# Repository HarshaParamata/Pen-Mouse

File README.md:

#  Pen Mouse – A Wireless Pen-Style Mouse using ATmega328P

The **Pen Mouse** is a compact, pen-like input device that functions similarly to a traditional mouse. It uses an optical sensor to detect movement and buttons for left/right click functionality. Built using affordable and widely available components, this device is ideal for students, designers, and users with limited desk space—particularly during presentations or graphic design work.

---

##  Features

- Move the cursor and perform clicks
- Pen-like ergonomic design for precise control
- Communicates wirelessly via Bluetooth
- Rechargeable and portable

---

##  Components Selection

- **ATmega328P-PU Microcontroller**  
  8-bit AVR RISC-based MCU with DIP-28 package for easy prototyping. Offers sufficient I/O, memory, and Arduino compatibility.

- **HC-06 Bluetooth Module (4-pin)**  
  Provides wireless connectivity. Simple UART interface, works with 3.3V or 5V logic.

- **TPS61023DRLT Switching Regulator**  
  Ensures stable 5V output from a Li-ion battery input, essential for reliable operation.
- **MX8733 Optical Sensor**
   it will track the movement of mouse send to microcontroller.
- **Li-ion Battery**  
  Rechargeable power source for portable use.

- **Arduino Uno**  
  Used for uploading firmware to the ATmega328P.

- **Passive Components (Resistors, Capacitors)**  
  For pull-ups, filtering, and power stabilization.

---
##  Getting Started

###  PCB Design

- The ATmega328P is placed centrally with decoupling capacitors near its power pins.
- SPI lines (MOSI, MISO, SCK, SS) are routed to the HC-06 Bluetooth module via pins 10–13 on the ATmega.
- A voltage regulation circuit using TPS61023DRLT generates a stable 5V from the Li-ion battery.

###  Uploading Code to ATmega328P

1. Use an **Arduino Uno as ISP** to program the ATmega328P.
2. Follow this official Arduino tutorial for setup and connections:  
    [How to program ATmega328P using Arduino Uno – Arduino to Breadboard](https://docs.arduino.cc/built-in-examples/arduino-isp/ArduinoToBreadboard/)
3. Or follow the  [youtude tutorials](https://youtube.com/playlist?list=PLtuqBdbsL-DvbB6QAGgoGBAEsGuXfGFoF&feature=shared).
4. Flash the Pen Mouse firmware (provided in the `codes/` folder).
5. After successful upload, remove the Arduino and power the Pen Mouse from the battery.
####  PINs VIvew of ATmega 328

##  Pen Mouse: Computer-Side Setup Guide (Windows/Linux/macOS)

This guide explains how to configure your computer to receive Pen Mouse input over Bluetooth and convert it into actual mouse movements using a Python script.

---

###  Prerequisites

- Python 3.6 or later
- Pip package manager
- HC-06 Bluetooth module paired with your system
- Basic code/text editor (e.g., Notepad++, VS Code, nano)

---

###  Step 1: Install Required Python Packages

Open your terminal or command prompt and run:

```bash

pip install pyserial pyautogui
```
### Step 2: Create and Save the Python Script

1. Open any code or text editor.
2. Copy the provided Python code for Pen Mouse control (refer to the codes section).
3. Save the file as `pen_mouse.py`.

###  Step 3: Pair HC-06 and Find Serial Port

####  Windows
- Pair HC-06 from **Settings > Devices > Bluetooth**.
- Open **Device Manager > Ports (COM & LPT)** to find the COM port (e.g., `COM5`).

####  Linux

```bash

bluetoothctl

scan on

pair XX:XX:XX:XX:XX:XX

trust XX:XX:XX:XX:XX:XX

connect XX:XX:XX:XX:XX:XX
```
```
ls /dev/rfcomm*
```
####  macOS
- Pair HC-06 via **System Preferences > Bluetooth**.
- Locate the device in Terminal:

```bash

ls /dev/tty.HC-06*
```
###  Step 4: Run the Script

Run the following command in terminal or command prompt:

```bash

python pen_mouse.py
```
Once running, your Pen Mouse should control the system cursor via Bluetooth.

---

###  Permissions and Troubleshooting

### Linux/macOS Serial Port Permissions

```bash

sudo chmod a+rw /dev/rfcomm0          # Linux

sudo chmod a+rw /dev/tty.HC-06-DevB   # macOS
```

####  macOS Accessibility Permissions

- Go to **System Preferences > Security & Privacy > Accessibility**
- Add and allow your Terminal or Python environment to control your mouse
###  References

- [PySerial Documentation](https://pyserial.readthedocs.io/)
- [PyAutoGUI Documentation](https://pyautogui.readthedocs.io/)

---

##  Hardware Snapshots

###  Schematic Diagram  

###  PCB Layout  

###  3D PCB View  

---

##  Repository Structure
```
PenMouse/  

├── kicad files/ # Schematic,BOM and PCB file 

├── images/ # Schematic and PCB images

├── datasheets/ # datasheet of components used

├── codes/ # code used for promgraming atmega and computer

├── Introduction # introduction and first idea of the project

├── PCB design # pcb design review

└── README.md

```
---

##  Future Improvements

- Add rechargeable support with USB charging
- Integrate gesture detection
- Replace HC-06 with BLE module for lower power and broader compatibility

---
## Team Members
 1. Kurre Vinay - EE23BTECH11036
 2. P.Harsha Vardan Kumar - EE23BTECH11214
 3. K S Ballavardhan - EE23BTECH11209
 4. Kailash C - EE23BTECH11207
 5. Manoj Kumar - EE23BTECH11211 

##  License

This project is licensed under the MIT License. See `LICENSE` file for details.

---

##  Contributing

Pull requests are welcome! For major changes, please open an issue first to discuss what you'd like to change.

---

##  Acknowledgements

- Inspired by DIY input devices and custom hardware projects
- Built at **IIT Hyderabad** as part of a ESDP Course Project

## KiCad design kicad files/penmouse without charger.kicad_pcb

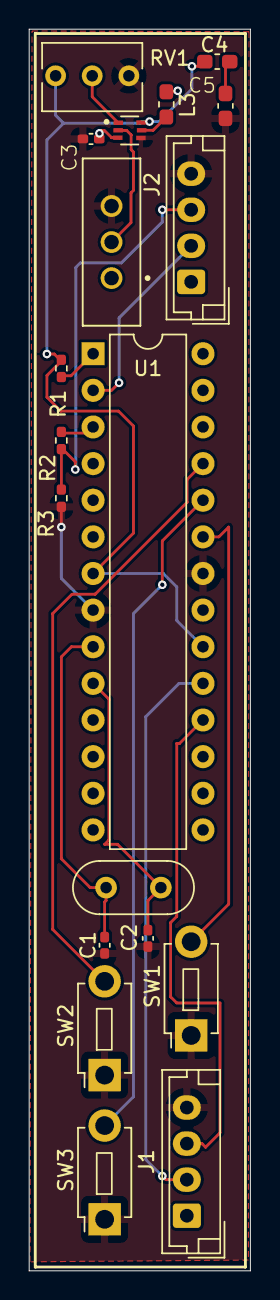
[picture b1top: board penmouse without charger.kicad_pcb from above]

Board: 2 copper layers, 15.3 x 86.1 mm, 19 parts (0 on the bottom side), 18 nets.

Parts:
C1, C2: 22p; C_0402_1005Metric_Pad0.74x0.62mm_HandSolder
C3: 10u; C_0402_1005Metric_Pad0.74x0.62mm_HandSolder
C4, C5: 22u; C_0603_1608Metric_Pad1.08x0.95mm_HandSolder
J1, J2: Conn_01x04_Socket; JST_EH_B4B-EH-A_1x04_P2.50mm_Vertical
L3: 1u; L_0603_1608Metric_Pad1.05x0.95mm_HandSolder
R1: 10k; R_0402_1005Metric_Pad0.72x0.64mm_HandSolder
R2: 2k; R_0402_1005Metric_Pad0.72x0.64mm_HandSolder
R3: 1k; R_0402_1005Metric_Pad0.72x0.64mm_HandSolder
RV1: R_Potentiometer; Potentiometer_Bourns_3266Y_Vertical
S2: EG1218; SW_EG1218
SW1, SW2, SW3: SW_Push; SW_PUSH_1P1T_6x3.5mm_H4.3_APEM_MJTP1243
U1: ATmega328P-P; DIP-28_W7.62mm
U3: TPS61023DRLT; SOT50P160X60-6N
Y2: Crystal; Crystal_HC52-8mm_Vertical

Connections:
GND: C1.1, C2.2, C3.1, C5.2, J1.4, J2.4, R3.2, RV1.1, S2.3, SW1.1, SW2.1, SW3.1, U1.8 (GND), U1.22 (GND), U3.4 (GND)
unnamed: C4.2, C5.1
unnamed: R2.2, U1.3 (PD1)
unnamed: C1.2, U1.9 (XTAL1/PB6), Y2.2
unnamed: C2.1, U1.10 (XTAL2/PB7), Y2.1
unnamed: R1.1, U1.1 (~RESET/PC6)
unnamed: S2.2, U3.2 (EN)
unnamed: RV1.2, U3.1 (FB)
unnamed: L3.2, U3.5 (SW)
Right: SW3.2, U1.24 (PC1)
left: SW1.2, U1.23 (PC0)
middle: SW2.2, U1.25 (PC2)
os1: J1.2, U1.19 (PB5)
os2: J1.3, U1.18 (PB4)
rx: J2.3, R2.1, R3.1
tx: J2.2, U1.2 (PD0)
vcc1: C3.2, J1.1, J2.1, L3.1, S2.1, U3.3 (VIN)
vcc2: C4.1, R1.2, RV1.3, U1.7 (VCC), U1.20 (AVCC), U3.6 (VOUT)

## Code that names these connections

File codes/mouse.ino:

#include <avr/io.h>
#include <util/delay.h>
#include <avr/interrupt.h>

#define F_CPU 16000000UL
#define BAUD_RATE 9600

// Define pins for buttons
#define LEFT_CLICK_PIN PC0
#define RIGHT_CLICK_PIN PC1

// Define MX8733B sensor pins
#define SENSOR_SCLK PB5
#define SENSOR_SDIO PB4
#define SENSOR_NCS PB3

// UART initialization
void UART_init(void) {
    uint16_t ubrr = F_CPU/16/BAUD_RATE - 1;
    UBRR0H = (unsigned char)(ubrr>>8);
    UBRR0L = (unsigned char)ubrr;
    UCSR0B = (1<<RXEN0)|(1<<TXEN0);
    UCSR0C = (1<<UCSZ01) | (1<<UCSZ00);
}

void UART_transmit(unsigned char data) {
    while (!(UCSR0A & (1<<UDRE0)));
    UDR0 = data;
}

// SPI functions for MX8733B
void SPI_init() {
    DDRB |= (1<<SENSOR_SCLK)|(1<<SENSOR_NCS);
    DDRB &= ~(1<<SENSOR_SDIO);
    PORTB |= (1<<SENSOR_NCS);
}

uint8_t SPI_transfer(uint8_t data) {
    uint8_t i;
    for (i = 0; i < 8; i++) {
        if (data & 0x80)
            PORTB |= (1<<SENSOR_SDIO);
        else
            PORTB &= ~(1<<SENSOR_SDIO);
        
        PORTB |= (1<<SENSOR_SCLK);
        _delay_us(1);
        data <<= 1;
        if (PINB & (1<<SENSOR_SDIO))
            data |= 1;
        PORTB &= ~(1<<SENSOR_SCLK);
        _delay_us(1);
    }
    return data;
}

void MX8733B_write(uint8_t address, uint8_t data) {
    PORTB &= ~(1<<SENSOR_NCS);
    SPI_transfer(address | 0x80);
    SPI_transfer(data);
    PORTB |= (1<<SENSOR_NCS);
}

uint8_t MX8733B_read(uint8_t address) {
    PORTB &= ~(1<<SENSOR_NCS);
    SPI_transfer(address);
    uint8_t data = SPI_transfer(0x00);
    PORTB |= (1<<SENSOR_NCS);
    return data;
}

void MX8733B_init() {
    _delay_ms(50);  // Power-up delay
    MX8733B_write(0x0D, 0x01);  // Enter configuration mode
    _delay_ms(1);
    MX8733B_write(0x0E, 0x80);  // Reset
    _delay_ms(1);
    MX8733B_write(0x0D, 0x00);  // Exit configuration mode
    _delay_ms(1);
}

int main(void) {
    UART_init();
    SPI_init();
    MX8733B_init();

    DDRC &= ~((1<<LEFT_CLICK_PIN)|(1<<RIGHT_CLICK_PIN));
    PORTC |= (1<<LEFT_CLICK_PIN)|(1<<RIGHT_CLICK_PIN);

    int8_t dx, dy;
    uint8_t buttons;

    while(1) {
        buttons = 0;
        if (!(PINC & (1<<LEFT_CLICK_PIN))) buttons |= 0x01;
        if (!(PINC & (1<<RIGHT_CLICK_PIN))) buttons |= 0x02;

        uint8_t motion = MX8733B_read(0x02);
        if (motion & 0x80) {
            dx = MX8733B_read(0x03);
            dy = MX8733B_read(0x04);
        } else {
            dx = dy = 0;
        }

        UART_transmit(buttons);
        UART_transmit(dx);
        UART_transmit(dy);

        _delay_ms(10);
    }

    return 0;
}

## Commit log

2025-03-16 Add files via upload
    This repository update includes KiCad designs, an updated Bill of Materials (BOM), and comprehensive reports. Key files include:
    Schematic (.kicad_sch) and PCB layout (.kicad_pcb) for circuit design.
    Drill files (.drl) for PCB fabrication.
    Updated BOM with component details.
    Reports summarizing design decisions and outcomes.
    PDF Documentation for quick reference.
2025-03-16 Delete Bill of Materials.xlsx
    Bill of materials has been removed to ensure accuracy and alignment with the updated component list.
2025-06-23 Create test
